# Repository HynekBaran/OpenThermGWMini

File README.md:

# OpenThermGWMini
## OpenTherm boiler hardware interface

HW interface connecting the boiler and Arduino (which may act as a thermostat). 
My boiler supports OpenTherm/Light (OT/-) protocol only and this is the only protocol I tested. 
As far as I know, hw (physical "electric" layer) specs of OT- and OT+ (2.0) are the same.

## Acknowledgments
This is just a copy of
http://jaagpad.blogspot.com/2011/09/opentherm-circuit-diagram.html

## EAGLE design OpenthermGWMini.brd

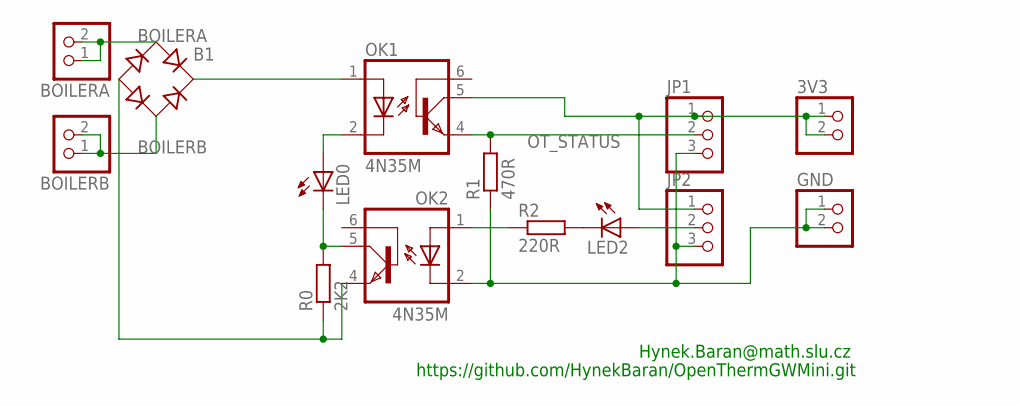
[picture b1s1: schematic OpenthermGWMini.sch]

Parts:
3V3: PINHD-1X2; 1X02
B1: RB1A
BOILERA: PINHD-1X2; 1X02
BOILERB: PINHD-1X2; 1X02
GND: PINHD-1X2; 1X02
JP1, JP2: PINHD-1X3; 1X03
LED0, LED2: LED3MM
OK1, OK2: 4N35M; DIL06
R0: 2K2; 0204/5
R1: 470R; 0204/5
R2: 220R; 0204/5

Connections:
3V3: 3V3.1, 3V3.2, JP1.1, JP2.1, OK1.5 (COL)
BOILERA: B1.AC1, BOILERA.1, BOILERA.2
BOILERB: B1.AC2, BOILERB.1, BOILERB.2
GND: GND.1, GND.2, JP1.3, JP2.3, OK2.2 (C), R1.1
unnamed: LED0.K (C), OK2.5 (COL), R0.2
unnamed: LED0.A, OK1.2 (C)
unnamed: OK2.1 (A), R2.1
unnamed: LED2.K (C), R2.2
OT+: B1.+, OK1.1 (A)
OT_GND: B1.-, OK2.4 (EMI), R0.1
OT_PWM: JP2.2, LED2.A
OT_STATUS: JP1.2, OK1.4 (EMI), R1.2

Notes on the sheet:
Hynek.Baran@math.slu.cz
https://github.com/HynekBaran/OpenThermGWMini.git

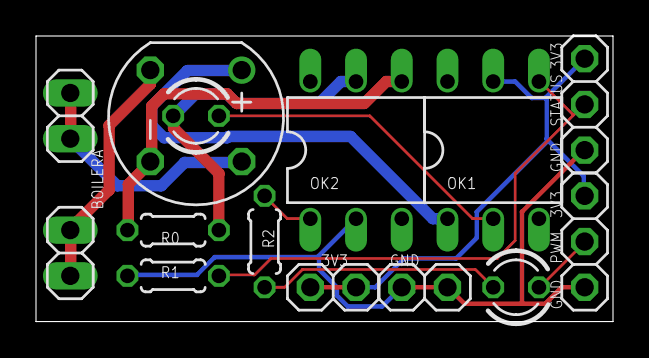
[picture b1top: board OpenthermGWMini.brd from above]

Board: 2 copper layers, 32.1 x 15.9 mm, 14 parts (0 on the bottom side), 12 nets.

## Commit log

2016-02-02 Initial commit https://oshpark.com/shared_projects/gVxQxmCj
2019-12-09 OpenthermGWMini.pdf
